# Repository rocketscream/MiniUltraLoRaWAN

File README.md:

# Mini Ultra LoRaWAN
An Arduino compatible ultra low power single cell LoRaWAN node powered by ATMega328P and RN2483A/RN2903A LoRaWAN module. Able to run off single 1.5V batteries (AAA, AA, C & D) or 3.0V CR123A battery that could last over a year.

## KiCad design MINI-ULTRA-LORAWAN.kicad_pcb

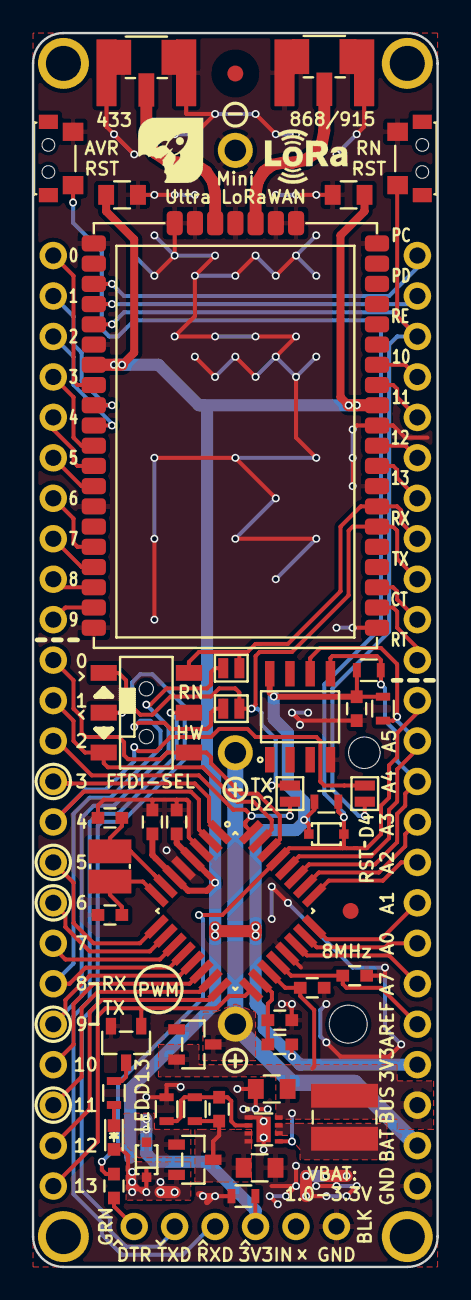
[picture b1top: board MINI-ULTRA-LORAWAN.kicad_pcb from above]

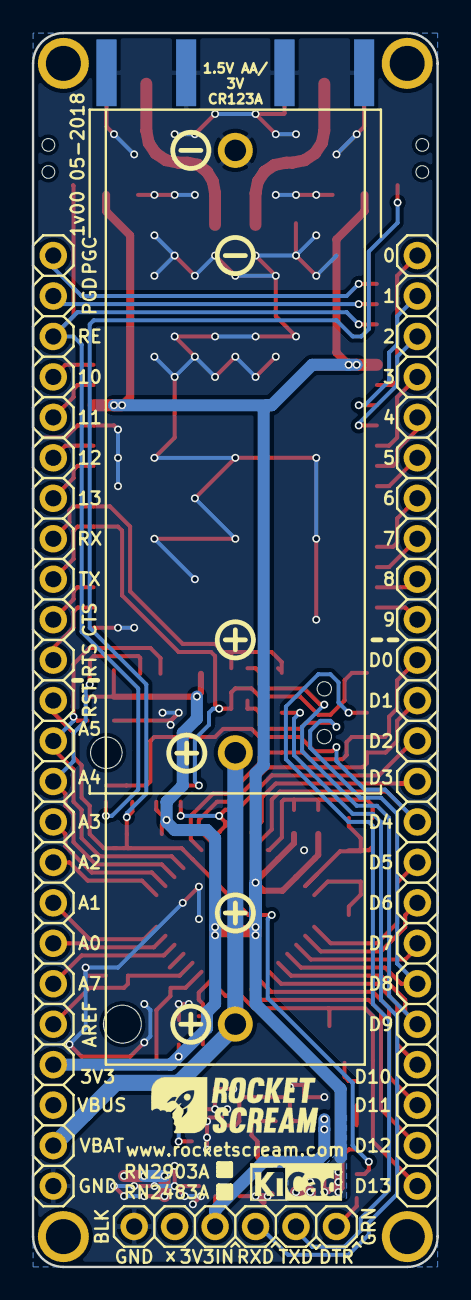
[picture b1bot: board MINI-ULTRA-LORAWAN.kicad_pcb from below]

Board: 2 copper layers, 25.4 x 77.5 mm, 59 parts (6 on the bottom side), 62 nets.

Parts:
BT1: CR123A/AA; 1028-1051
C1, C2, C5, C6, C7, C9, C12: 100nF; C_0603
C3, C8, C10, C11: 47uF 10V X5R; C_0805
C4, C13: 10pF; C_0603
C14: 47pF; C_0603
D1: 1N4148; SOD-323
D2: Red; LED_0603
D3: PMEG3010CEJ; SOD-323
J1: 2.54 mm 1x6; HDR_1x6_Pitch2.54mm
J2, J3: 2.54 mm 1x24; HDR_1x24_Pitch2.54mm
J4, J6: RF-SMA-EDGE_Without_Feed
J5, J7: U.FL-R-SMT; U.FL-R-SMT_Extended
JP1, JP2, JP3, JP4: JUMPER-1-WAY; JUMPER-1-WAY-SMD
L1: LBMF1608T100K; I_0603
L2: SRN4012TA-R47M; SRN4012TA
LOGO1: LOGO-KICAD; LOGO-KICAD_XXXSmall
LOGO2: LOGO-ROCKET-SCREAM; LOGO-ROCKET-SCREAM_Horizontal_XXSmall
LOGO3: LOGO-LORA; LOGO-LORA_XSmall
LOGO4: LOGO-ROCKET-SCREAM; LOGO-ROCKET-SCREAM_Without_Text_XXXSmall
M1, M2: FIDUCIAL; FIDUCIAL-1MM
M3, M4, M5, M6: MOUNT_HOLE; HOLE_PTH_2.2MM
Q1: 2N7002; SOT-23
Q2, Q3: DMP2035U; SOT-23
R1, R7: 10K; R_0603
R2, R5, R6: 2K2; R_0603
R3: 100K; R_0603
R4: 316K; R_0603
SW1, SW3: SPNO; TS-018
SW2: IS-1390
U1: TPS61021ADSG; WSON-8
U2: ATMEGA328P-AU; TQFP-32_7x7mm_Pitch0.8mm
U3: RN2483; RN2xx3
U4: ATECC508A-SSHDA; SOIC-8-N_8S1
Y1: NX3225GD

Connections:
3V3: C1.1, C2.1, C10.1, C11.1, C12.1, D1.1, D2.2, D3.1, J3.21, L1.2, Q3.2, R1.1, R5.1, R6.1, U2.4, U2.6, U3.12, U3.34, U4.8
3V3IN: D3.2, J1.4, Q3.1, R7.1
3V3OUT: C8.1, C14.1, Q3.3, R4.2, U1.3, U1.4
/A0: J3.18, U2.23
/A1: J3.17, U2.24
/A2: J3.16, U2.25
/A3: J3.15, U2.26
/A4: J3.14, R6.2, U2.27, U4.5
/A5: J3.13, R5.2, U2.28, U4.6
/A7: J3.19, U2.22
/CTS: J3.10, U3.3
/D0: J2.11, SW2.4, U2.30
/D1: J2.12, SW2.3, U2.31
/D2: J2.13, JP4.1, U2.32
/D3: J2.14, U2.1
/D4: J2.15, JP1.1, U2.2
/D5: J2.16, U2.9
/D6: J2.17, U2.10
/D7: J2.18, U2.11
/D8: J2.19, JP2.1, U2.12
/D9: J2.20, JP3.1, U2.13
/D10: J2.21, U2.14
/D11: J2.22, U2.15
/D12: J2.23, U2.16
/D13: J2.24, Q1.1, U2.17
/GPIO0: J2.1, U3.35
/GPIO1: J2.2, U3.36
/GPIO2: J2.3, U3.37
/GPIO3: J2.4, U3.38
/GPIO4: J2.5, U3.39
/GPIO5: J2.6, U3.40
/GPIO6: J2.7, U3.43
/GPIO7: J2.8, U3.44
/GPIO8: J2.9, U3.45
/GPIO9: J2.10, U3.46
/GPIO10: J3.4, U3.14
/GPIO11: J3.5, U3.13
/GPIO12: J3.6, U3.10
/GPIO13: J3.7, U3.9
/PGC: J3.1, U3.30
/PGD: J3.2, U3.31
/RESET: J3.3, JP1.2, SW3.2, U3.32
/RST: C6.1, D1.2, J3.12, R1.2, SW1.1, U2.29
/RTS: J3.11, U3.2
/RX: J3.8, JP3.2, SW2.6, U3.7
/RXD: J1.3, SW2.5
/TX: J3.9, JP2.2, JP4.2, SW2.1, U3.6
/TXD: J1.2, SW2.2
AREF: C7.1, J3.20, U2.20
GND: BT1.2, C1.2, C2.2, C3.2, C4.2, C5.2, C7.2, C8.2, C9.2, C10.2, C11.2, C12.2, C13.2, J1.6, J3.24, J4.2, J4.3, J4.4, J4.5, J5.2, J5.3, J6.2, J6.3, J6.4, J6.5, J7.2, J7.3, Q1.2, Q2.1, R3.2, R7.2, SW1.2, SW3.1, U1.1, U1.9, U2.3, U2.5, U2.21, U3.1, U3.8, U3.11, U3.20, U3.21, U3.22, U3.24, U3.26, U3.27, U3.28, U3.33, U3.41, U3.47, U4.4
unnamed: C4.1, U2.7, Y1.1
unnamed: C5.1, L1.1, U2.18
unnamed: C6.2, J1.1
unnamed: C13.1, U2.8, Y1.2
unnamed: C14.2, R3.1, R4.1, U1.2
unnamed: D2.1, R2.2
unnamed: J5.1, U3.23
unnamed: J7.1, U3.25
unnamed: L2.2, U1.6, U1.7
unnamed: Q1.3, R2.1
VBAT: BT1.1, J3.23, Q2.3
VBUS: C3.1, C9.1, J3.22, L2.1, Q2.2, U1.5, U1.8, U2.19

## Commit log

2018-08-04 R1.00
2018-08-19 Added example on OTAA with TTN
2018-09-04 Enclosure
2018-09-04 Add TTN decoder
2018-09-04 Documentation fix
2018-09-05 Fix for CR123A battery
